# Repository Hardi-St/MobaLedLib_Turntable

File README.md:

# MobaLedLib
## Turntable Control

### This repository contains the software and the hardware files for a Arduino based turntable control

**Features:**
- Uses a stepper motor for exact positioning
- Manual control using a poti
- Automatic control per rotation switch
- Control by command program using DCC, Selectrix or CAN
- OLED Display
- Sound generation
- Polarisation relais
- ...

**Attention:** This is the first version. Not all features are finished yet

Details could be found here:
https://stummiforum.de/viewtopic.php?t=188668

Contact: MobaLedLib@gmx.de

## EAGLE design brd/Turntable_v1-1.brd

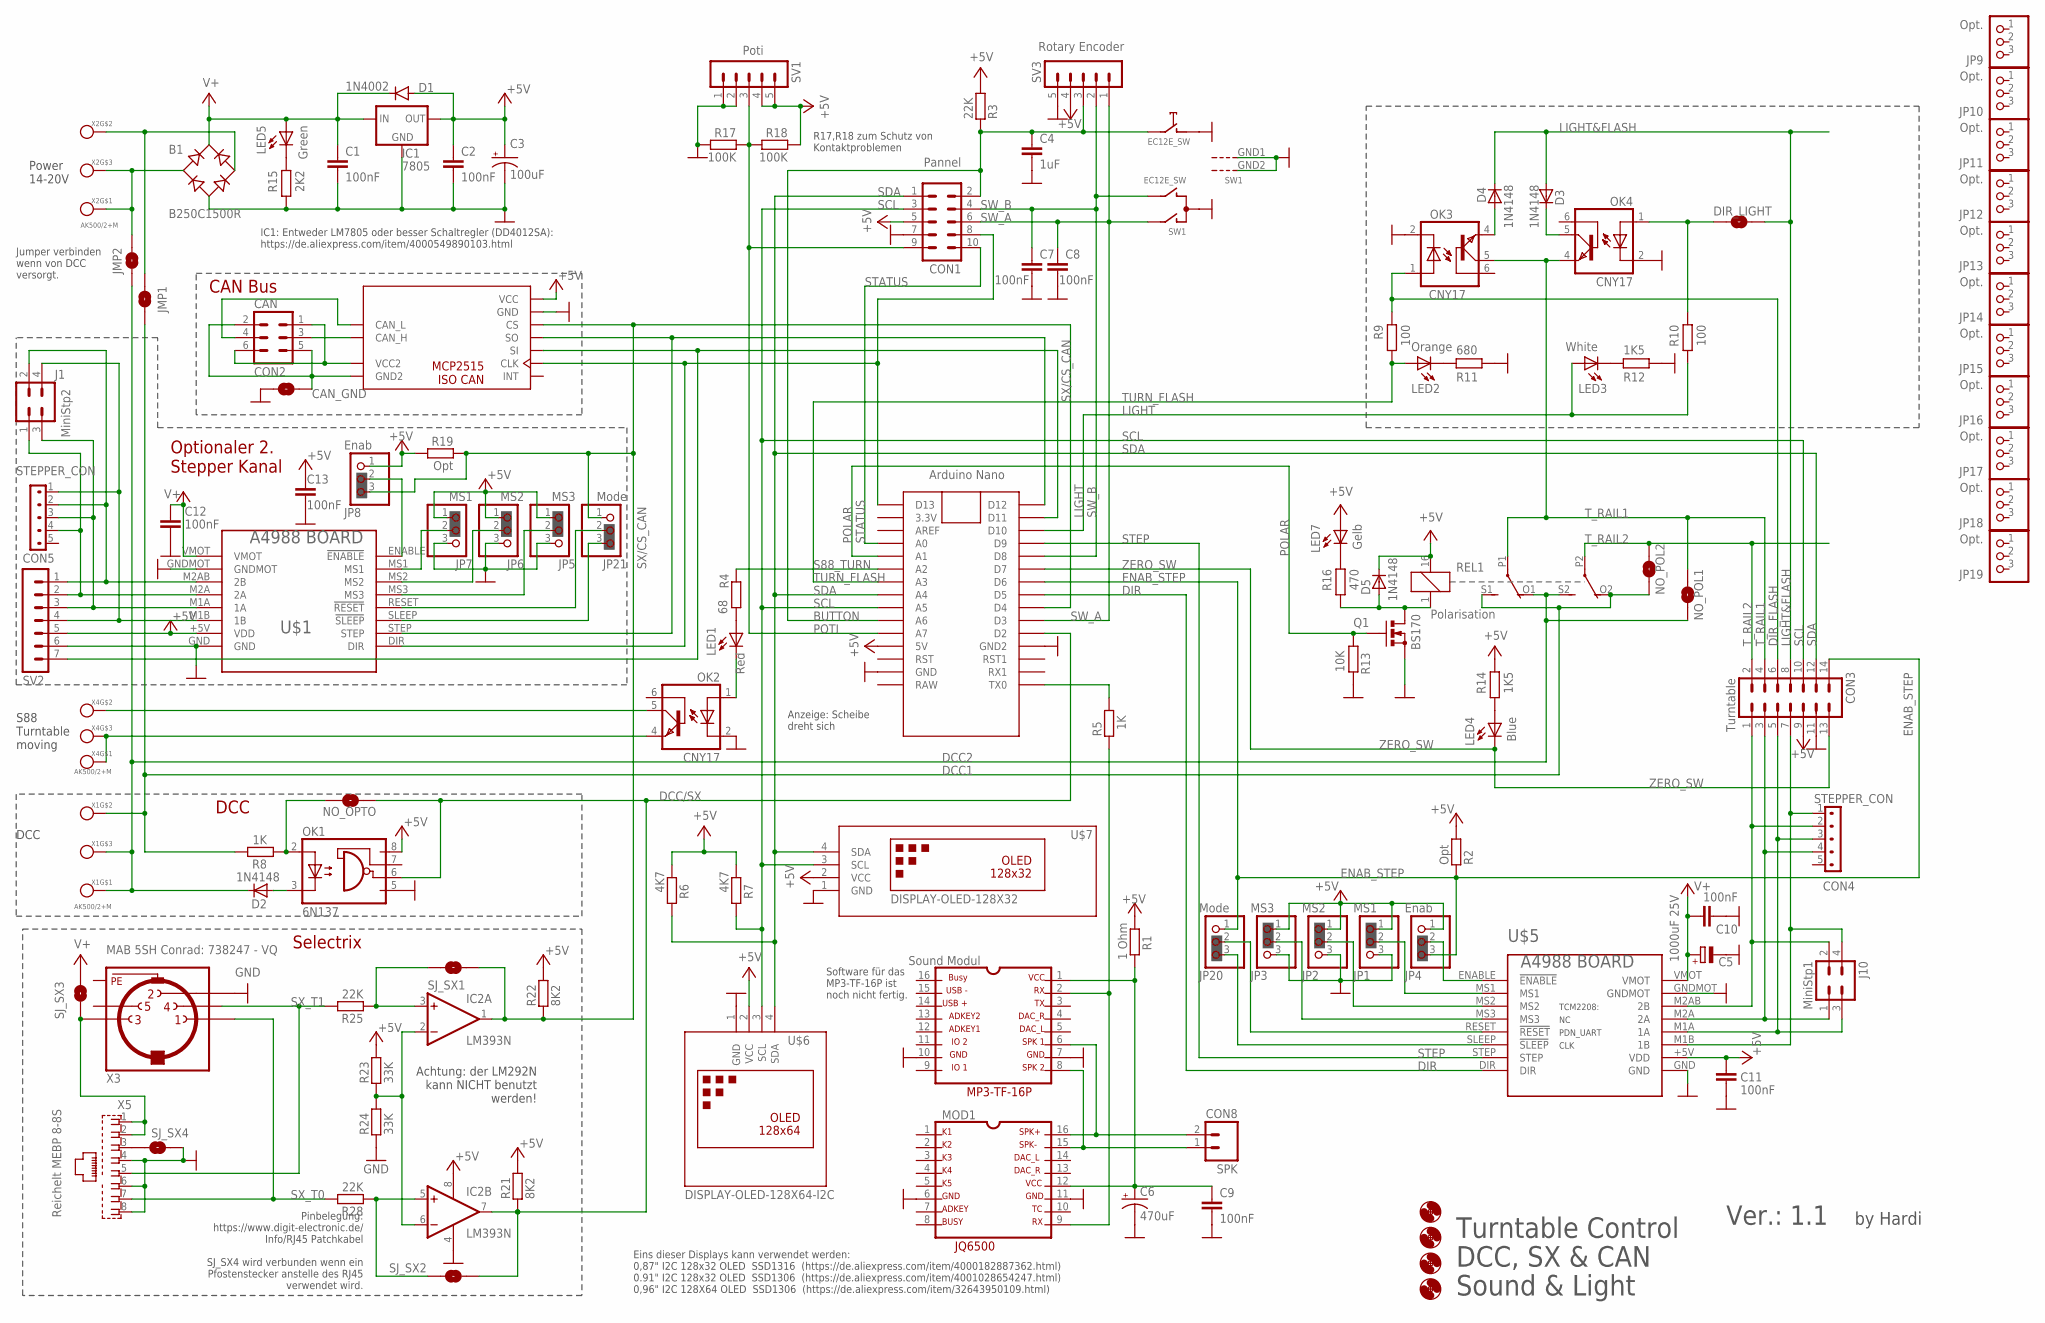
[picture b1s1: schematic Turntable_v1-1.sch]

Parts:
B1: B250C1500R; RB1A
C1, C2, C7, C8, C9, C10, C11, C12, C13: 100nF; C050-024X044
C3: 100uF; SPARKFUN-CAPACITORS_CPOL-RADIAL-100UF-25V
C4: 1uF; C050-024X044
C5: 1000uF 25V; E5-10,5
C6: 470uF; SPARKFUN-CAPACITORS_CPOL-RADIAL-100UF-25V
CAN1: MCP2515_ISO_CAN
CAN_GND: SOLDERJUMPERNO; SJ_2S-NO
CON1: Pannel; ML10
CON2: CAN; ML6
CON3: Turntable; ML14
CON4, CON5: STEPPER_CON
CON8: SPK; 1X02
D1: 1N4002; DO41-10
D2, D3, D4, D5: 1N4148; DO35-7
DIR_LIGHT: SOLDERJUMPERNO; SJ_2S-NO
H1, H2, H3, H4: MOUNT-HOLE3.0; 3,0
IC1: 7805; 78XXS
IC2: LM393N; DIL08
J1: MiniStp2; CON-HARTING-ML_ML4
J10: MiniStp1; CON-HARTING-ML_ML4
JMP1, JMP2: SOLDERJUMPERNO; SJ_2S-NO
JP1, JP7: MS1; 1X03-CLEANBIG
JP2, JP6: MS2; 1X03-CLEANBIG
JP3, JP5: MS3; 1X03-CLEANBIG
JP4, JP8: Enab; 1X03-CLEANBIG
JP9, JP10, JP11, JP12, JP13, JP14, JP15, JP16, JP17, JP18, JP19: Opt.; 1X03-CLEANBIG
JP20, JP21: Mode; 1X03-CLEANBIG
LED1: Red; LED3MM
LED2: Orange; LED3MM
LED3: White; LED3MM
LED4: Blue; LED3MM
LED5: Green; LED3MM
LED7: Gelb; LED3MM
MOD1: JQ6500
MOD2: Sound Modul; MP3-TF-16P_MP3-TF-16P
NO_OPTO: SOLDERJUMPERNO; SJ_2S-NO
NO_POL1, NO_POL2: SOLDERJUMPERNO; SJ_2S-NO
OK1: 6N137; DIL08
OK2, OK3, OK4: CNY17; DIL06
Q1: BS170; SOT54E
R1: 1 Ohm; RCL_0204/7
R2, R19: Opt; 0204/7
R3, R25, R28: 22K; 0204/7
R4: 68; 0204/7
R5, R8: 1K; 0204/7
R6, R7: 4K7; RCL_0204/7
R9, R10: 100; 0204/7
R11: 680; 0204/7
R12, R14: 1K5; 0204/7
R13: 10K; 0204/7
R15: 2K2; 0204/7
R16: 470; 0204/7
R17, R18: 100K; 0204/7
R21, R22: 8K2; 0204/7
R23, R24: 33K; 0204/7
REL1: Polarisation; 351
SJ_SX1, SJ_SX2, SJ_SX3, SJ_SX4: SOLDERJUMPERNO; SJ_2S-NO
SV1: Poti; MA05-1
SV2: MA07-1
SV3: Rotary Encoder; MA05-1_SMALL_PAD
SW1: EC12E_SW; ALPS_EC12E_SW
U2: LED NANO; NANO
U$1, U$5: BOARD_A4988
U$6: DISPLAY-OLED-128X64-I2C
U$7: DISPLAY-OLED-128X32
X1, X2, X4: AK500/2+M
X3: MAB 5SH Conrad: 738247 - VQ; MAB5SH
X5: Reichelt MEBP 8-8S; RJ45_MEBP8-8S

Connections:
+5V: C2.1, C3.1 (+), C11.1, C13.1, CAN1.1 (VCC), CON1.5, CON3.9, D1.A, D5.C, IC1.OUT, IC2.8 (V+), JP1.1, JP2.1, JP3.1, JP4.1, JP5.1, JP6.1, JP7.1, JP8.1, LED7.A, OK1.8 (VCC), R1.1, R2.2, R3.2, R6.1, R7.1, R14.1, R18.1, R19.2, R21.2, R22.2, R23.2, REL1.16 (2), SV1.4, SV1.5, SV2.5, SV3.4, U2.5V, U$1.+5V (VDD), U$5.+5V (VDD), U$6.2 (VCC), U$7.2 (VCC)
BUTTON: C4.1, CON1.2, R3.1, SV3.3, SW1.E (2), U2.A6
CAN_H: CAN1.9 (CAN_H), CON2.3
CAN_L: CAN1.8 (CAN_L), CON2.4
D11: CAN1.5 (SI), SV2.7, U2.D11
D12: CAN1.4 (SO), U2.D12, U$1.STEP
DCC1: JMP1.2, NO_POL2.2, R8.2, REL1.O2 (O), REL1.S1 (S), X1.2
DCC2: D2.C, JMP2.2, NO_POL1.2, REL1.O1 (O), REL1.S2 (S), X1.1, X1.M
DCC/SX: IC2.7 (OUT), NO_OPTO.1, OK1.6 (VO), R21.1, SJ_SX2.2, U2.D2
DIR: U2.D5, U$5.DIR
DIR_FLASH: CON3.6, OK3.1 (A), R9.1
ENAB_STEP: CON3.14, JP4.3, JP20.1, R2.1, U2.D6
GND: B1.-, C1.2, C2.2, C3.2 (-), C4.2, C5.-, C6.2 (-), C7.2, C8.2, C9.2, C10.2, C11.2, C12.2, C13.2, CAN1.2 (GND), CAN_GND.2, CON1.7, CON3.11, IC1.GND, IC2.4 (V-), JP1.3, JP2.3, JP3.3, JP5.3, JP6.3, JP7.3, MOD1.6, MOD1.11, MOD2.7, MOD2.10, OK1.5 (GND), OK2.2 (C), OK3.2 (C), OK4.2 (C), Q1.S, R11.2, R12.2, R13.2, R15.2, R17.2, R24.1, SJ_SX4.2, SV1.1, SV1.2, SV2.6, SV3.5, SW1.C, SW1.D (1), SW1.GND1 (G), SW1.GND2 (G), U2.GND, U2.GND1 (GND2), U$1.GND, U$1.GNDMOT, U$5.GND, U$5.GNDMOT, U$6.1 (GND), U$7.1 (GND), X3.2, X5.4, X5.6, X5.8
LIGHT: LED3.A, R10.2, U2.D10
LIGHT&FLASH: CON3.8, D3.A, D4.C, DIR_LIGHT.2
unnamed: JP5.2, U$1.MS3
unnamed: SJ_SX4.1, X5.3
unnamed: CAN1.11 (GND2), CAN_GND.1, CON2.2, CON2.5
unnamed: C6.1 (+), C9.1, MOD1.12, MOD2.1, R1.2
unnamed: CAN1.6 (CLK), CON1.8, U2.D13, U$1.DIR
unnamed: CON8.1, MOD1.15, MOD2.8
unnamed: MOD1.9, MOD2.2, R5.1
unnamed: LED1.K (C), OK2.1 (A)
unnamed: CON8.2, MOD1.16, MOD2.6
unnamed: CAN1.10 (VCC2), CON2.1, CON2.6
unnamed: R5.2, U2.TX0
unnamed: B1.AC2, JMP1.1, X2.2
unnamed: B1.AC1, JMP2.1, X2.1, X2.M
unnamed: JP2.2, U$5.MS2
unnamed: D2.A, OK1.3 (C)
unnamed: LED2.K (C), R11.1
unnamed: D5.A, Q1.D, R16.2, REL1.1
unnamed: LED1.A, R4.1
unnamed: OK2.4 (EMI), X4.1, X4.M
unnamed: OK2.5 (COL), X4.2
unnamed: NO_OPTO.2, OK1.2 (A), R8.1
unnamed: JP1.2, U$5.MS1
unnamed: LED3.K (C), R12.1
unnamed: LED4.A, R14.2
unnamed: JP4.2, U$5.ENABLE (!ENABLE)
unnamed: SJ_SX3.1, X3.3, X5.1, X5.2
unnamed: JP3.2, U$5.MS3
unnamed: D4.A, OK3.4 (EMI)
unnamed: D3.C, OK4.5 (COL)
unnamed: JP20.2, U$5.RESET (!RESET)
unnamed: CON3.1, CON4.2, J10.2, U$5.M2AB (2B)
unnamed: JP21.3, U$1.SLEEP (!SLEEP)
unnamed: JP20.3, U$5.SLEEP (!SLEEP)
unnamed: LED5.K (C), R15.1
unnamed: CON3.7, CON4.1, J10.4, U$5.M1B (1B)
unnamed: LED7.K (C), R16.1
unnamed: DIR_LIGHT.1, OK4.1 (A), R10.1
unnamed: IC2.2 (-IN), IC2.6 (-IN), R23.1, R24.2
unnamed: IC2.3 (+IN), R25.1, SJ_SX1.1
unnamed: CON3.3, CON4.4, J10.1, U$5.M2A (2A)
unnamed: CON3.5, CON4.3, J10.3, U$5.M1A (1A)
unnamed: IC2.5 (+IN), R28.1, SJ_SX2.1
unnamed: JP6.2, U$1.MS2
unnamed: JP7.2, U$1.MS1
unnamed: JP8.2, U$1.ENABLE (!ENABLE)
unnamed: JP21.2, U$1.RESET (!RESET)
unnamed: CON5.2, J1.2, SV2.1, U$1.M2AB (2B)
unnamed: CON5.4, J1.1, SV2.2, U$1.M2A (2A)
unnamed: CON5.3, J1.3, SV2.3, U$1.M1A (1A)
unnamed: CON5.1, J1.4, SV2.4, U$1.M1B (1B)
PE: X3.PE, X3.PE@ (PE)
POLAR: Q1.G, R13.1, U2.A1
POTI: CON1.9, R17.1, R18.2, SV1.3, U2.A7
S88_TURN: R4.2, U2.A2
SCL: CON1.3, CON3.10, R7.2, U2.A5, U$6.3 (SCL), U$7.3 (SCL)
SDA: CON1.1, CON3.12, R6.2, U2.A4, U$6.4 (SDA), U$7.4 (SDA)
STATUS: CON1.10, U2.A0
STEP: U2.D9, U$5.STEP
SW_A: C8.1, CON1.6, SV3.1, SW1.A, U2.D3
SW_B: C7.1, CON1.4, SV3.2, SW1.B, U2.D8
SX/CS_CAN: CAN1.3 (CS), IC2.1 (OUT), JP8.3, JP21.1, R19.1, R22.1, SJ_SX1.2, U2.D4
SX_T0: R28.2, X3.1, X5.7
SX_T1: R25.2, X3.4, X5.5
TURN_FLASH: LED2.A, R9.2, U2.A3
T_RAIL1: CON3.4, NO_POL1.1, OK3.5 (COL), OK4.4 (EMI), REL1.P1
T_RAIL2: CON3.2, NO_POL2.1, REL1.P2
V+: B1.+, C1.1, C5.+, C10.1, C12.1, D1.C, IC1.IN, LED5.A, SJ_SX3.2, U$1.VMOT, U$5.VMOT
ZERO_SW: CON3.13, LED4.K (C), U2.D7

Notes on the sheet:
Pinbelegung: https://www.digit-electronic.de/ Info/RJ45 Patchkabel SJ_SX4 wird verbunden wenn ein Pfostenstecker anstelle des RJ45 verwendet wird.
Achtung: der LM292N kann NICHT benutzt werden!
DCC
IC1: Entweder LM7805 oder besser Schaltregler (DD4012SA): https://de.aliexpress.com/item/4000549890103.html
by Hardi
Ver.: 1.1
Turntable Control DCC, SX & CAN Sound & Light
S88 Turntable moving
Power 14-20V
R17,R18 zum Schutz von Kontaktproblemen
Optionaler 2. Stepper Kanal
Jumper verbinden wenn von DCC versorgt.
Anzeige: Scheibe dreht sich
Software für das MP3-TF-16P ist noch nicht fertig.
DCC
CAN Bus
Selectrix
Eins dieser Displays kann verwendet werden: 0,87" I2C 128x32 OLED SSD1316 (https://de.aliexpress.com/item/4000182887362.html) 0.91" I2C 128x32 OLED SSD1306 (https://de.aliexpress.com/item/4001028654247.html) 0,96" I2C 128X64 OLED SSD1306 (https://de.aliexpress.com/item/32643950109.html)
TCM2208: NC PDN_UART CLK

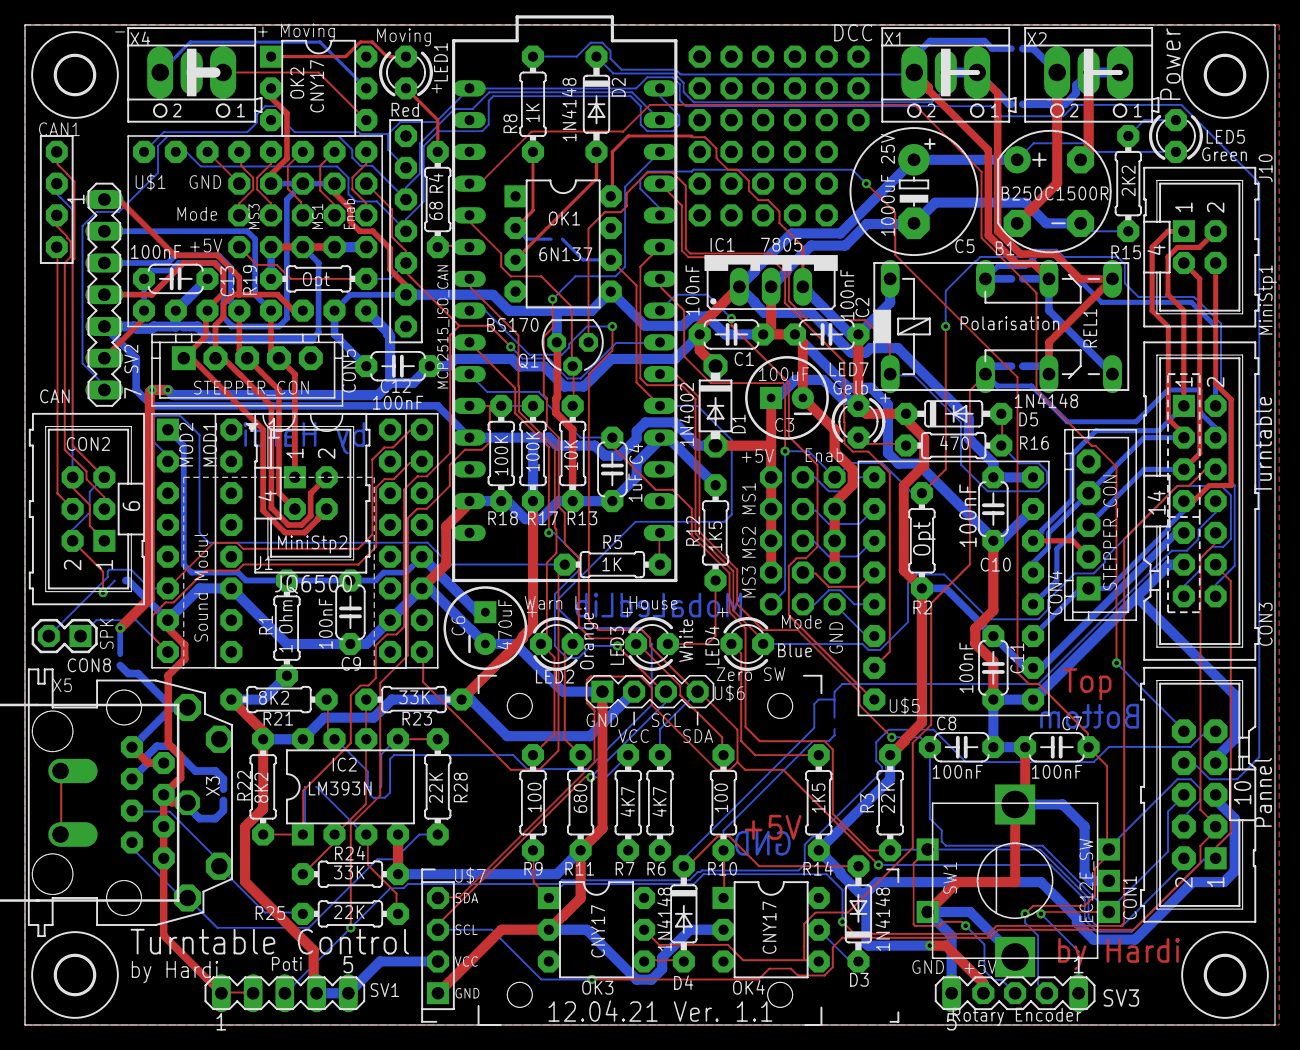
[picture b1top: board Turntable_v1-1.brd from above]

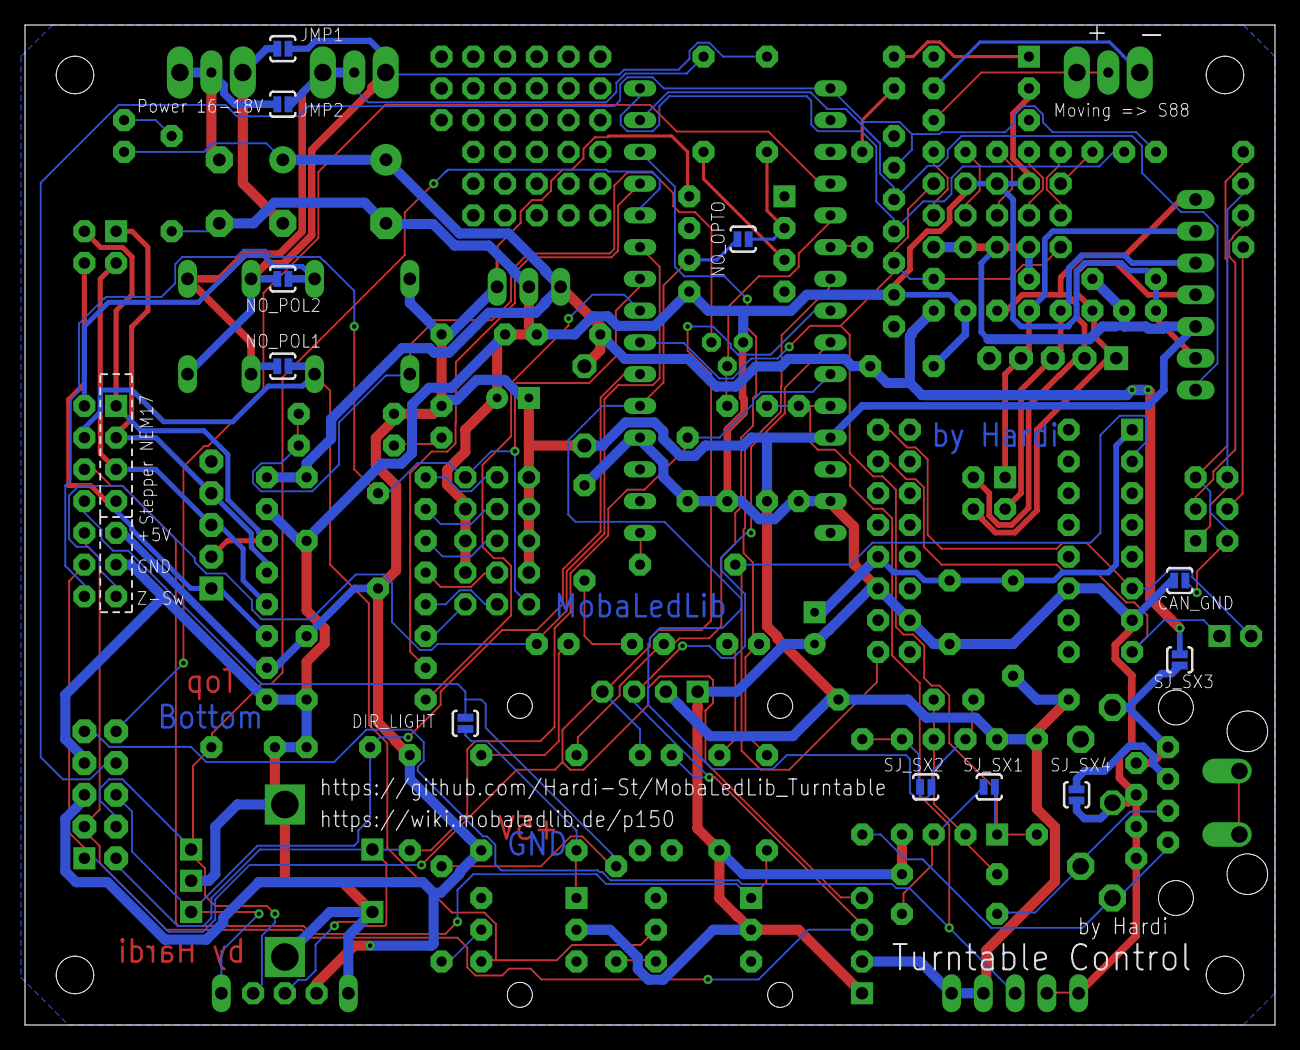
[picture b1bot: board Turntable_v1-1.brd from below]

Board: 2 copper layers, 100.0 x 80.0 mm, 119 parts (11 on the bottom side), 83 nets.

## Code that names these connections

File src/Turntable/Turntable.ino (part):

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            - Port number could be selected in the "Save position" menu only once at the beginning to
              prevent wrong sequences. Call "Reset all" to change the sequence.
            - Moved the poti to A7 because A0 could also be used as output. This could be changed with:
                #define POTI_PIN A0
            - Moved the rotation switch button to A6. This could be changed with:
                #define ENCODER_SW_PIN 9
              to the old pin number in the config file
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 08.01.21:  - Last menu position is stored. By default the "Reverse" line is activated
              => A double click could be used to reverse the turntable.
              This is also useful to save the port positions...
            - Stopping fast if the poti is turned to 0. Prior the time depends on the last speed.
            - Added MOVING_FLASH_INVERS
            - Filling also the port positions of the oposite direction with standard values when the first
              port in oposite direction is defined
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#endif

#ifndef SPEED_POTI_DIRECTION
#define SPEED_POTI_DIRECTION                1           // Set to -1 to change the direction of the speed poti
#endif

// *** Pins ***
#ifndef POTI_PIN
#define POTI_PIN                            A7          // Pin used for the speed potentiometer
#endif
#ifndef ENCODER_A_PIN
#define ENCODER_A_PIN                       3           // Best Performance: both pins have interrupt capability
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#ifndef NOT_ENABLE_PIN
#define NOT_ENABLE_PIN                      6           // Set to -1 if the stepper driver has an automatic power mode like the TMC2100
#endif                                                  // The pin of the module must be left open
#ifndef ZERO_SW_PIN
#define ZERO_SW_PIN                         7           // Switch connected to GND or low active reflex coupler
#endif
#ifndef STATUS_LED_PIN
#define STATUS_LED_PIN                      LED_BUILTIN
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#define SOUND_VOLUME2                       20          // Set the volume by the DCC addr DCC_VOLUME_2_ADDR
#endif

#ifndef LIGHT_PIN
#define LIGHT_PIN                           10          // Light in the machine house on the turntable
#endif


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#endif

#ifndef ANALOG_SPEED_DIVISOR
#define ANALOG_SPEED_DIVISOR                8           // Divisor used to calculate the analog speed with the poti
#endif
#ifndef MIN_ANALOG_SPEED                                // Speed in steps/10sec. If the minimal speed is to small the repons time is to high
#define MIN_ANALOG_SPEED                    20          // 1 => 10 sec reaction time ;-(   Reaction time = 10 sec / MIN_ANALOG_SPEED
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#define DCC_PLAY_SOUND8_ADDR                DCC_ADD_DIR(220, GRN)       // Play sound 8
#endif
#ifndef DCC_DISABLE_LIGHT_ADDR
#define DCC_DISABLE_LIGHT_ADDR              DCC_ADD_DIR(221, RED)       // Disable the light in the machine house on the turntable
#endif
#ifndef DCC_ENABLE_LIGHT_ADDR
#define DCC_ENABLE_LIGHT_ADDR               DCC_ADD_DIR(221, GRN)       // Enable the light
#endif
#ifndef DCC_SET_SPEED1_ADDR
#define DCC_SET_SPEED1_ADDR                 DCC_ADD_DIR(222, RED)       // Set the moving speed to MOVE_SPEED1
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#endif

#ifndef STORE_DCC_SWITCHES_TO_EEPROM
#define STORE_DCC_SWITCHES_TO_EEPROM        1                           // Store the Switches for sound and light to the EEPROM
#endif


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#define DEBOUNCE_ZERO                       50          // Debouncing of the zero switch in mirco steps (500 was needed for the optical reflex detection)
#endif
#ifndef SPEED_POTI_MID_RANGE
#define SPEED_POTI_MID_RANGE                100         // Range of the speed poti which is 0  (Old 50)
#endif
#ifndef SPEED_POTI_CENTER
#define SPEED_POTI_CENTER                   512         // Center position of the speed poti (Normaly 512)
#endif

#ifndef ENABLE_ALWAYS_ON                                // Set to 1 for a powerful stepper without gearbox because the magnetic field will change the position when powered of
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bool Get_Zero_SW()
//----------------
{
  return !digitalRead(ZERO_SW_PIN); // "!" because it's Low active
}

#if USE_JQ6500_SERIAL
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{
  #if DCC_ENABLE_LIGHT_ADDR != -1 || DCC_DISABLE_LIGHT_ADDR != -1
      if (On)
           FastPin<LIGHT_PIN>::hi();
      else FastPin<LIGHT_PIN>::lo();
      #if STORE_DCC_SWITCHES_TO_EEPROM
          ee.Flags.Light = On;
          Write_EEPROM();
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  Step1.setRampLen(STEPPER_RAMP_LENGTH);  // Beschleunigung

  FastPin<STATUS_LED_PIN>::setOutput();
  pinMode(ZERO_SW_PIN,    INPUT_PULLUP);
  pinMode(ENCODER_SW_PIN, INPUT_PULLUP);

  #if WS281X_DATA_PIN >= 0
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  #endif


  #if LIGHT_PIN != -1
    FastPin<LIGHT_PIN>::setOutput();
  #endif

  Restore_DCC_Switches();
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//---------------------
{
  #if USE_AVDWEB_ANALOGREADFAST
    uint16_t Value = analogReadFast(POTI_PIN);
  #else
    uint16_t Value = analogRead(POTI_PIN);
  #endif

  #define ANALOG_FILTER 4
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
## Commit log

2021-01-28 First Version
2021-01-28 Correchted spelling
2021-01-31 Corrected Potary Encoder Pins
2021-02-02 Final Version 1.0
2021-02-15 Updated LM292 Text
2021-04-12 Update 2021-04-12
    + R6 and R7, PullUps for I2C
    ~ CAN-Modul VCC to +5V
2021-04-13 Version 1.1
    + R6 and R7, PullUps for I2C
    ~ CAN-Modul: changed VCC to +5V
2021-05-29 Update Link
2021-11-02 Added 1.3" OLED and Speed Up I2C

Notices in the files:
parts and their libraries:
SparkFun-Retired: Licensing:Creative Commons ShareAlike 4.0 International - https://creativecommons.org/licenses/by-sa/4.0
diy-modules: Released under the Creative Commons Attribution 4.0 International License: http://creativecommons.org/licenses/by/4.0
